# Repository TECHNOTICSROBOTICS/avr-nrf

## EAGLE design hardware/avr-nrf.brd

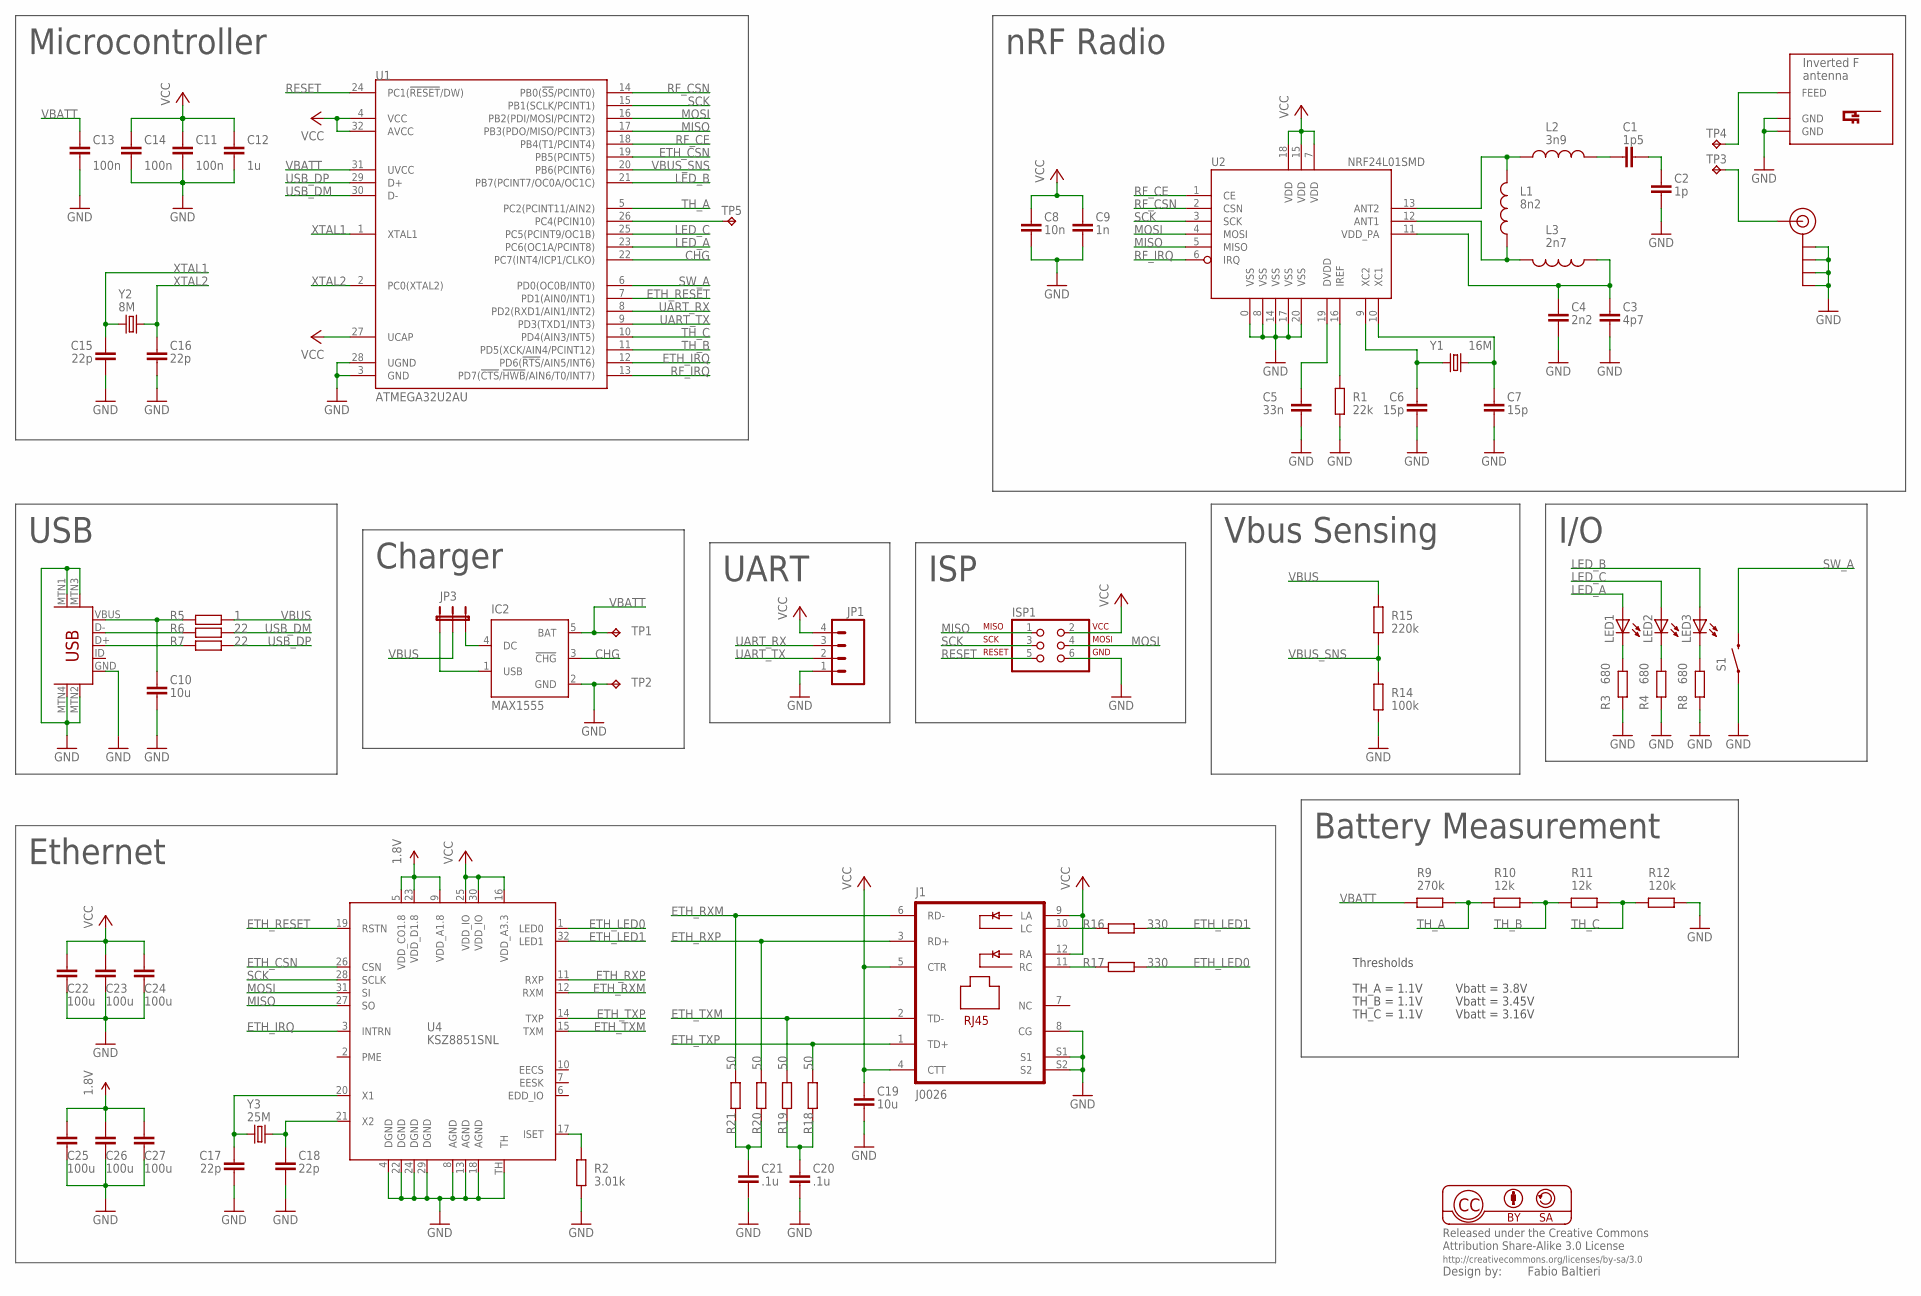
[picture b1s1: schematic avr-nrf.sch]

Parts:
C1: 1p5; C0805
C2: 1p; C0805
C3: 4p7; C0805
C4: 2n2; C0805
C5: 33n; C0805
C6, C7: 15p; C0805
C8: 10n; C0805
C9: 1n; C0805
C10, C19: 10u; C0805
C11, C13, C14: 100n; C0805
C12: 1u; C0805
C15, C16, C17, C18: 22p; C0805
C20, C21: .1u; C0805
C22, C23, C24, C25, C26, C27: 100u; C0805
IC2: MAX1555; SOT23-5L
ISP1: ISP-AVR910PTH; 2X03
J1: J0026; PJ-J0
J$1: SMA_EDGE; SMA-EDGE
JP1: M04PTH; 1X04
JP3: JUMPER-3SMD; SJ_3
L1: 8n2; 0603
L2: 3n9; 0603
L3: 2n7; 0603
LED1, LED2, LED3: LEDCHIPLED_0805; CHIPLED_0805
R1: 22k; R0603
R2: 3.01k; R0603
R3, R4, R8: 680; R0603
R5: 1; R0603
R6, R7: 22; R0603
R9: 270k; R0603
R10, R11: 12k; R0603
R12: 120k; R0603
R14: 100k; R0603
R15: 220k; R0603
R16, R17: 330; R0603
R18, R19, R20, R21: 50; R0603
S1: SWITCH-MOMENTARY-2SMD; TACTILE_SWITCH_SMD
TP1, TP2: TPTP12R; TP12R
TP3, TP4: TPTP08SQ; TP08SQ
TP5: TPTP06R; TP06R
U1: ATMEGA32U2AU; TQFP32-08
U2: NRF24L01SMD; QFN20
U3: USB-MINIB-5PIN; USB-MINIB
U4: KSZ8851SNL; MLF32-TH
U$1: INVERTED_F_ANTENNA+5; DN007+5
Y1: 16M; CRYSTAL-SMD-5X3
Y2: 8M; CRYSTAL-SMD-5X3
Y3: 25M; CRYSTAL-SMD-5X3

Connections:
1.8V: C25.1, C26.1, C27.1, U4.5 (VDD_CO1.8), U4.9 (VDD_A1.8), U4.23 (VDD_D1.8)
CHG: IC2.3 (!CHG), U1.22 (PC7(INT4/ICP1/CLKO))
ETH_CSN: U1.19 (PB5(PCINT5)), U4.26 (CSN)
ETH_IRQ: U1.12 (PD6(!RTS!/AIN5/INT6)), U4.3 (INTRN)
ETH_LED0: R17.2, U4.1 (LED0)
ETH_LED1: R16.2, U4.32 (LED1)
ETH_RESET: U1.7 (PD1(AIN0/INT1)), U4.19 (RSTN)
ETH_RXM: J1.6 (RD-), R21.2, U4.12 (RXM)
ETH_RXP: J1.3 (RD+), R20.2, U4.11 (RXP)
ETH_TXM: J1.2 (TD-), R19.2, U4.15 (TXM)
ETH_TXP: J1.1 (TD+), R18.2, U4.14 (TXP)
GND: C2.2, C3.2, C4.2, C5.2, C6.2, C7.2, C8.2, C9.2, C10.2, C11.2, C12.2, C13.2, C14.2, C15.2, C16.2, C17.2, C18.2, C19.2, C20.2, C21.2, C22.2, C23.2, C24.2, C25.2, C26.2, C27.2, IC2.2 (GND), ISP1.6, J1.8 (CG), J1.S1, J1.S2, J$1.GND@0 (GND), J$1.GND@1 (GND), J$1.GND@2 (GND), J$1.GND@3 (GND), JP1.1, R1.2, R2.2, R3.2, R4.2, R8.2, R12.1, R14.2, S1.1, TP2.TP, U1.3 (GND), U1.28 (UGND), U2.0 (VSS), U2.8 (VSS), U2.14 (VSS), U2.17 (VSS), U2.20 (VSS), U3.GND, U3.MTN1 (MTN2), U3.MTN2 (MTN3), U3.MTN3 (MTN1), U3.MTN4, U4.4 (DGND), U4.8 (AGND), U4.13 (AGND), U4.18 (AGND), U4.22 (DGND), U4.24 (DGND), U4.29 (DGND), U4.TH, U$1.GND, U$1.GND@1 (GND)
LED_A: LED1.A, U1.23 (PC6(OC1A/PCINT8))
LED_B: LED3.A, U1.21 (PB7(PCINT7/OC0A/OC1C))
LED_C: LED2.A, U1.25 (PC5(PCINT9/OC1B))
MISO: ISP1.1, U1.17 (PB3(PDO/MISO/PCINT3)), U2.5 (MISO), U4.27 (SO)
MOSI: ISP1.4, U1.16 (PB2(PDI/MOSI/PCINT2)), U2.4 (MOSI), U4.31 (SI)
unnamed: L1.2, L3.2, U2.12 (ANT1)
unnamed: L1.1, L2.1, U2.13 (ANT2)
unnamed: C1.1, L2.2
unnamed: C1.2, C2.1
unnamed: C3.1, C4.1, L3.1, U2.11 (VDD_PA)
unnamed: J$1.SIG (SIGNAL), TP3.TP
unnamed: C5.1, U2.19 (DVDD)
unnamed: R1.1, U2.16 (IREF)
unnamed: C7.1, U2.10 (XC1), Y1.3 (2)
unnamed: C6.1, U2.9 (XC2), Y1.1
unnamed: TP4.TP, U$1.FEED
unnamed: IC2.4 (DC), JP3.3
unnamed: R7.1, U3.D+
unnamed: R6.1, U3.D-
unnamed: LED1.C, R3.1
unnamed: IC2.1 (USB), JP3.1
unnamed: LED2.C, R4.1
unnamed: LED3.C, R8.1
unnamed: J1.10 (LC), R16.1
unnamed: J1.11 (RC), R17.1
unnamed: R2.1, U4.17 (ISET)
unnamed: C17.1, U4.20 (X1), Y3.1
unnamed: C18.1, U4.21 (X2), Y3.3 (2)
unnamed: TP5.TP, U1.26 (PC4(PCIN10))
unnamed: C21.1, R20.1, R21.1
unnamed: C20.1, R18.1, R19.1
unnamed: C10.1, R5.1, U3.VBUS
RESET: ISP1.5, U1.24 (PC1(!RESET!/DW))
RF_CE: U1.18 (PB4(T1/PCINT4)), U2.1 (CE)
RF_CSN: U1.14 (PB0(!SS!/PCINT0)), U2.2 (CSN)
RF_IRQ: U1.13 (PD7(!CTS!/!HWB!/AIN6/T0/INT7)), U2.6 (IRQ)
SCK: ISP1.3, U1.15 (PB1(SCLK/PCINT1)), U2.3 (SCK), U4.28 (SCLK)
SW_A: S1.3 (2), U1.6 (PD0(OC0B/INT0))
TH_A: R9.1, R10.2, U1.5 (PC2(PCINT11/AIN2))
TH_B: R10.1, R11.2, U1.11 (PD5(XCK/AIN4/PCINT12))
TH_C: R11.1, R12.2, U1.10 (PD4(AIN3/INT5))
UART_RX: JP1.3, U1.8 (PD2(RXD1/AIN1/INT2))
UART_TX: JP1.2, U1.9 (PD3(TXD1/INT3))
USB_DM: R6.2, U1.30 (D-)
USB_DP: R7.2, U1.29 (D+)
VBATT: C13.1, IC2.5 (BAT), R9.2, TP1.TP, U1.31 (UVCC)
VBUS: JP3.2, R5.2, R15.1
VBUS_SNS: R14.1, R15.2, U1.20 (PB6(PCINT6))
VCC: C8.1, C9.1, C11.1, C12.1, C14.1, C19.1, C22.1, C23.1, C24.1, ISP1.2, J1.4 (CTT), J1.5 (CTR), J1.9 (LA), J1.12 (RA), JP1.4, U1.4 (VCC), U1.27 (UCAP), U1.32 (AVCC), U2.7 (VDD), U2.15 (VDD), U2.18 (VDD), U4.16 (VDD_A3.3), U4.25 (VDD_IO), U4.30 (VDD_IO)
XTAL1: C15.1, U1.1 (XTAL1), Y2.1
XTAL2: C16.1, U1.2 (PC0(XTAL2)), Y2.3 (2)

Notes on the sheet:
USB
UART
Microcontroller
ISP
Charger
nRF Radio
I/O
Battery Measurement
Vbus Sensing
Ethernet
Thresholds
TH_A = 1.1V
TH_C = 1.1V
TH_B = 1.1V
Vbatt = 3.8V
Vbatt = 3.45V
Vbatt = 3.16V

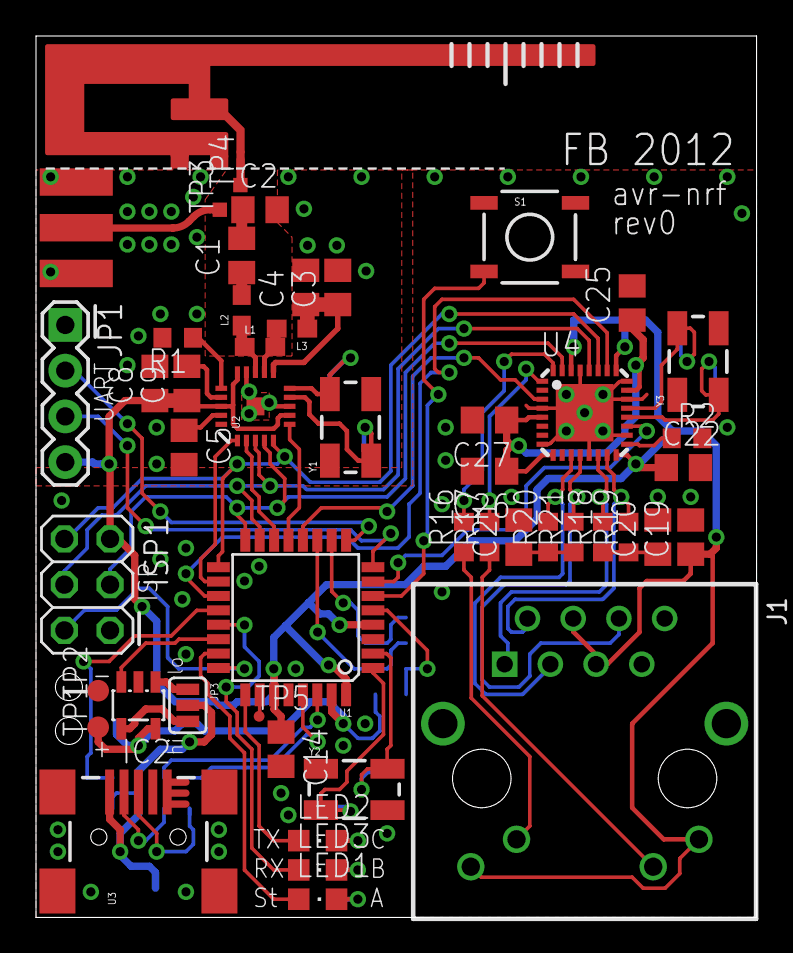
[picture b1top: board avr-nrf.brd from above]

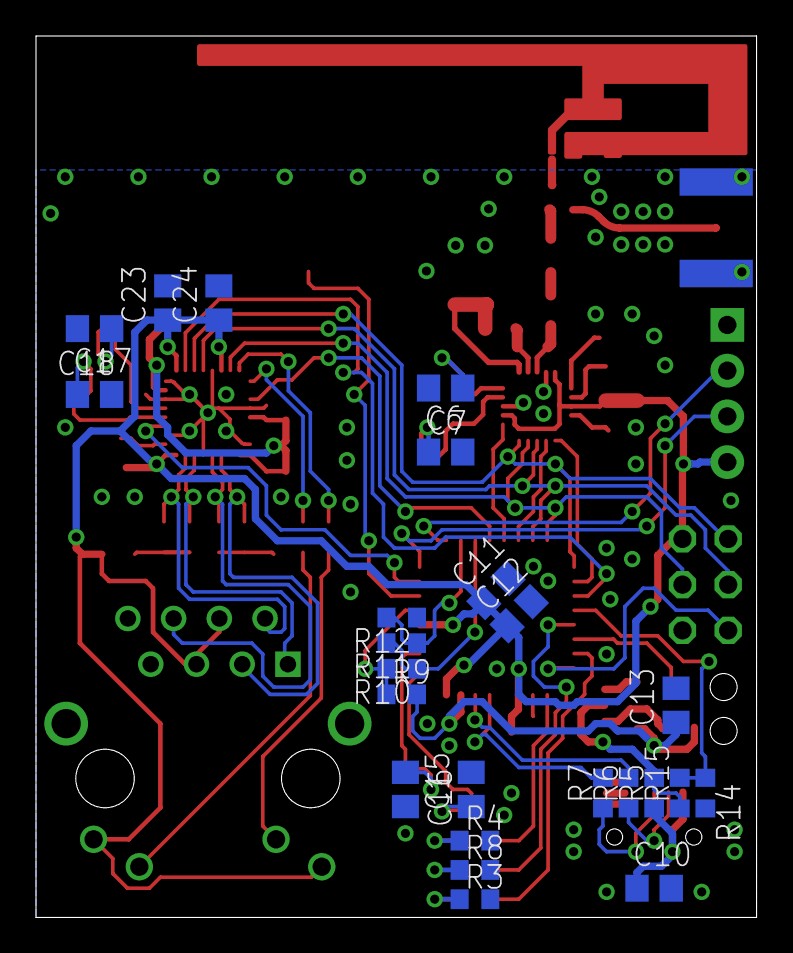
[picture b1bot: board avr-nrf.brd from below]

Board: 2 copper layers, 40.0 x 49.0 mm, 73 parts (24 on the bottom side), 63 nets.

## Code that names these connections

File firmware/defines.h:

/* buttons */
#define BUTTON_PORT PORTD
#define BUTTON_DDR  DDRD
#define BUTTON_PIN  PIND
#define BUTTON PD0

#define button_init() do { BUTTON_PORT |= _BV(BUTTON); } while (0)
#define button_read() (!(BUTTON_PIN & _BV(BUTTON)))

/* leds */
#define LED_A_PORT PORTC
#define LED_A_DDR  DDRC
#define LED_A PC6
#define LED_B_PORT PORTB
#define LED_B_DDR DDRB
#define LED_B PB7
#define LED_C_PORT PORTC
#define LED_C_DDR DDRC
#define LED_C PC5

#define led_init() do {                                         \
	                LED_A_DDR |= _BV(LED_A);                        \
	                LED_B_DDR |= _BV(LED_B);                        \
	                LED_C_DDR |= _BV(LED_C);                        \
	        } while (0)

#define led_a_on()     LED_A_PORT |=  _BV(LED_A)
#define led_a_off()    LED_A_PORT &= ~_BV(LED_A)
#define led_a_toggle() LED_A_PORT ^=  _BV(LED_A)
#define led_b_on()     LED_B_PORT |=  _BV(LED_B)
#define led_b_off()    LED_B_PORT &= ~_BV(LED_B)
#define led_c_on()     LED_C_PORT |=  _BV(LED_C)
#define led_c_off()    LED_C_PORT &= ~_BV(LED_C)

/* Charger */
#define CHG_PORT        PORTC
#define CHG_PIN         PINC
#define CHG             PC7

#define chg_init() CHG_PORT |= _BV(CHG)
#define chg_read() (!(CHG_PIN & _BV(CHG)))

/* Battery thresholds */
#define THA_PIN	PINC
#define THA	PC2
#define THB_PIN	PIND
#define THB	PD5
#define THC_PIN	PIND
#define THC	PD4

#define tha_read() (THA_PIN & _BV(THA))
#define thb_read() (THB_PIN & _BV(THB))
#define thc_read() (THC_PIN & _BV(THC))
#define th_read()  ((!!tha_read() << 0) | (!!thb_read() << 1) | (!!thc_read() << 2))

/* SPI */
#define SPI_DDR  DDRB
#define SPI_PORT PORTB
#define SPI_SS   PB0
#define SPI_SCK  PB1
#define SPI_MOSI PB2
#define SPI_MISO PB3

/* nRF24L01+ SPI */
#define NRF_DDR  DDRB
#define NRF_PORT PORTB
#define NRF_CS   SPI_SS
#define NRF_CE   PB4

#define nrf_cs_h() (NRF_PORT |=  _BV(NRF_CS))
#define nrf_cs_l() (NRF_PORT &= ~_BV(NRF_CS))
#define nrf_ce_h() (NRF_PORT |=  _BV(NRF_CE))
#define nrf_ce_l() (NRF_PORT &= ~_BV(NRF_CE))

/* KSZ8851SNL SPI */
#define ETH_DDR  DDRB
#define ETH_PORT PORTB
#define ETH_CS   PB5

#define eth_cs_h() (ETH_PORT |=  _BV(ETH_CS))
#define eth_cs_l() (ETH_PORT &= ~_BV(ETH_CS))

/* Interrupts */
#define BUTTON_EICR	EICRA
#define BUTTON_ISC	((0 << ISC01) | (1 << ISC00))
#define BUTTON_INT	INT0

#define CHG_INT		INT4
#define CHG_EICR	EICRB
#define CHG_ISC		((0 << ISC41) | (1 << ISC40))

#define ETH_INT		INT6
#define ETH_EICR	EICRB
#define ETH_ISC		((1 << ISC61) | (0 << ISC60))

#define NRF_INT		INT7
#define NRF_EICR	EICRB
#define NRF_ISC		((0 << ISC71) | (0 << ISC70))

#define irq_init() do {					  \
		BUTTON_EICR |= BUTTON_ISC;		  \
		CHG_EICR |= CHG_ISC;			  \
		ETH_EICR |= ETH_ISC;			  \
		NRF_EICR |= NRF_ISC;			  \
		EIMSK |= _BV(BUTTON_INT) | _BV(CHG_INT) | \
			_BV(ETH_INT) | _BV(NRF_INT);	  \
	} while (0)

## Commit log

2011-12-04 hardware: initial schematics and brd import
2011-12-04 add battery calculator utility
2011-12-04 hardware: add antenna library
2011-12-04 gitignore: add gitignore file
2011-12-04 hardware: updated layout
2011-12-05 hardware: implemented stefano's notes
2011-12-05 hardware: layout improvements
2011-12-05 hardware: minor layout updates
2011-12-05 hardware: other layout improvements
2011-12-05 hardware: last update for today
2011-12-11 hardware: change qfn pads shape to pass DRC
2011-12-11 hardware: redraw antenna to pass DRC tests
2011-12-11 hardware: add silkscreen
2011-12-15 hardware: modify rf gnd layout, add border vias
2011-12-26 hardware: convert to eagle 6 format (xml)
2012-04-02 hardware: fix eth cap values
2012-04-02 firmware: initial commit
2012-04-02 firmware: shiny new Makefile
2012-04-02 firmware: ep0: add nrf write/read reg
2012-04-02 firmware: move cs init from drivers to main
2012-04-02 firmware: add preliminary ksz8851snl driver
2012-04-03 firmware: ksz8851: add irq stubs
2012-04-05 .gitignore: add .d files
2012-05-01 nrf24l01: add ce_l to nrf_powerup
2012-05-04 firmware: add charging indicator
2012-05-05 hw: antenna: add pre-cut variants
2012-05-05 hw: update antenna symbol on schematics
2012-05-06 hw: add no-eth variant
2012-05-06 hw: add irq code
2012-05-06 fw: add power_down code
2012-05-08 fw: fix vendor id mispell
2012-05-09 fw: add th defines
2012-05-09 fw: add 8MHz support
2012-05-09 fw: nrf: change channel to 24 (less wifi-g interferences)
2012-05-09 Revert "fw: add power_down code"
    This reverts commit 23964ade6c0fe154e3c36222626aa786d36f36f9.
2012-05-09 fw: add some test code
2012-05-09 fw: minor cosmetic changes
2012-05-09 fw: move led blink in wdt isr
2012-05-09 fw: add can_suspend functions
2012-05-10 fw: usb: add suspend support
2012-05-10 fw: board: rewrite reset function
2012-05-10 fw: main: change wdt timeout
2012-05-10 fw: main: enable power down mode
2012-05-10 fw: blink: rework blink code
2012-05-10 fw: suspend: add suspend_check
2012-05-10 fw: main: better blink logic
2012-05-10 fw: main: add button suspend check
2012-05-10 fw: main: slow down standby blink rate
2012-05-13 fw: nrf: rename mode functions
2012-05-13 fw: nrf: change tx pulse length to 10us
2012-05-13 fw: usb: change ep configuration
2012-05-13 fw: add fifo files
2012-05-13 fw: add missing gpl headers
2012-05-13 fw: nrf: add fifo push for rx
2012-05-13 fw: add fifo_full, fix Makefile
2012-05-13 fw: main: add basic usb packet handling
2012-05-13 fw: main: protect main loop fifo accesses
2012-05-13 fw: implement fifo tx
2012-05-13 fw: nrf: additional check on wake_queue
2012-05-13 fw: main: missing blank
2012-05-13 main: add debug_tx function
2012-05-13 main: missing static identifier from hello
2012-05-13 fw: make nrf irq level sensitive
2012-05-13 fw: implement power control
    Turn RX off when running without usb connectivity
2012-05-13 fw: add board id functions
2012-05-13 fw: add node id to debug msg
2012-05-13 fw: fifo: reduce fifo size to 4 packets
2012-05-13 fw: main: remove literals for payload size
2012-05-13 scripts: add board-id
2012-05-14 fw: blink: blink faster
2012-05-14 fw: main: blink each second
2012-05-14 fw: nrf: powerdown only when necessary
2012-08-31 Makefile: remove redundant -Os
2012-09-02 decode: add decode utility
2012-09-02 decode: rename nrf_packet to nrf_frame
2012-09-02 fw: use nrf_frame
2012-09-04 decode: fix makefile deps
2012-09-04 decode: add struct nrf_power and dumping
2012-09-08 fw/decode: update packet format
2012-11-10 decode: add vbatt charging print
2012-11-10 decode: add timestamping
2012-11-10 decode: fix gcc 4.7 warnings
2012-11-10 decode: add stdin support
2012-11-10 decode: make dump_power BE safe
2012-11-11 decode: initial usb support
2012-11-11 decode: working direct usb
2012-11-11 decode: add flush, better help
2012-11-11 decode: retry on timeout
2012-11-12 fw: add if0'ed debug stuff
2012-11-13 fw: fix button init
2012-11-15 fw: main: init button
2012-11-15 fw: add missing vital ksz driver functions
2012-11-15 fw: add initial net files
2012-11-15 main: add basic net support
2012-11-15 sw: blink: add jiffies!
2012-11-15 fw: net: use jiffies for timing
2012-11-16 decode: add claim/unclaim commands
2012-11-16 fw: ksz881snl: fix read function
2012-11-19 decode: add EAGAIN to retry error list
2012-11-25 decode: add net stubs
2012-11-25 decode: add udp stubs
2012-11-25 fw: ksz: initialize ret in read_packet
2012-11-25 fw: led: rework led blink code
2012-11-25 fw: main: disable power down mode
2012-11-25 fw: Makefile: do not reset after programming
2012-11-25 fw: unbind on button press
2012-11-25 fw: net: change osc ids
2012-11-25 fw: net: relay nrf packets vie network
2012-11-25 fw: net: change bound osc path
2012-11-25 fw: nrf: keep rx on
2012-11-25 fw: net: unbind after 10 secs
2012-11-25 fw: nrf: rework bound function
2012-11-25 fw: net: put strings in define
2012-11-26 decode: add missing net sources
2012-11-27 fw: net: beacon every second
2012-11-27 decode: first net code working
2012-11-27 decode: net: implement keepalive
2012-11-27 decode: net: remove debug stuff
2012-11-29 fw: Makefile: drop unused text data
2012-11-29 fw: net: add multicast test code
2012-11-29 decode: add multicast support
2012-11-29 fw: net: missed a blank line
2012-11-29 decode: missing double bind
2012-12-11 net: add ipv6 support code
2012-12-11 net: ipv6 mcast send function
2013-01-28 Makefile: drop extra cflags
2013-01-28 fw: support runtime mode change
2013-01-28 fw: Makefile: use /bin/bash as SHELL
    This fixes a build error on stock ubuntu installation that uses dash for
    /bin/sh.
2013-02-06 decode: very dirt commit to add direct rrdtool support
2013-05-03 hack: print only sensor 0x20
2013-06-29 fw: nrf_frames: declare nrf_msg on its own
2013-12-25 nrf_frames: add boot defines
2013-12-25 decode: decode boot frames

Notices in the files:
parts and their libraries:
balto: Released under the Creative Commons
balto: http://creativecommons.org/licenses/by-sa/3.0
